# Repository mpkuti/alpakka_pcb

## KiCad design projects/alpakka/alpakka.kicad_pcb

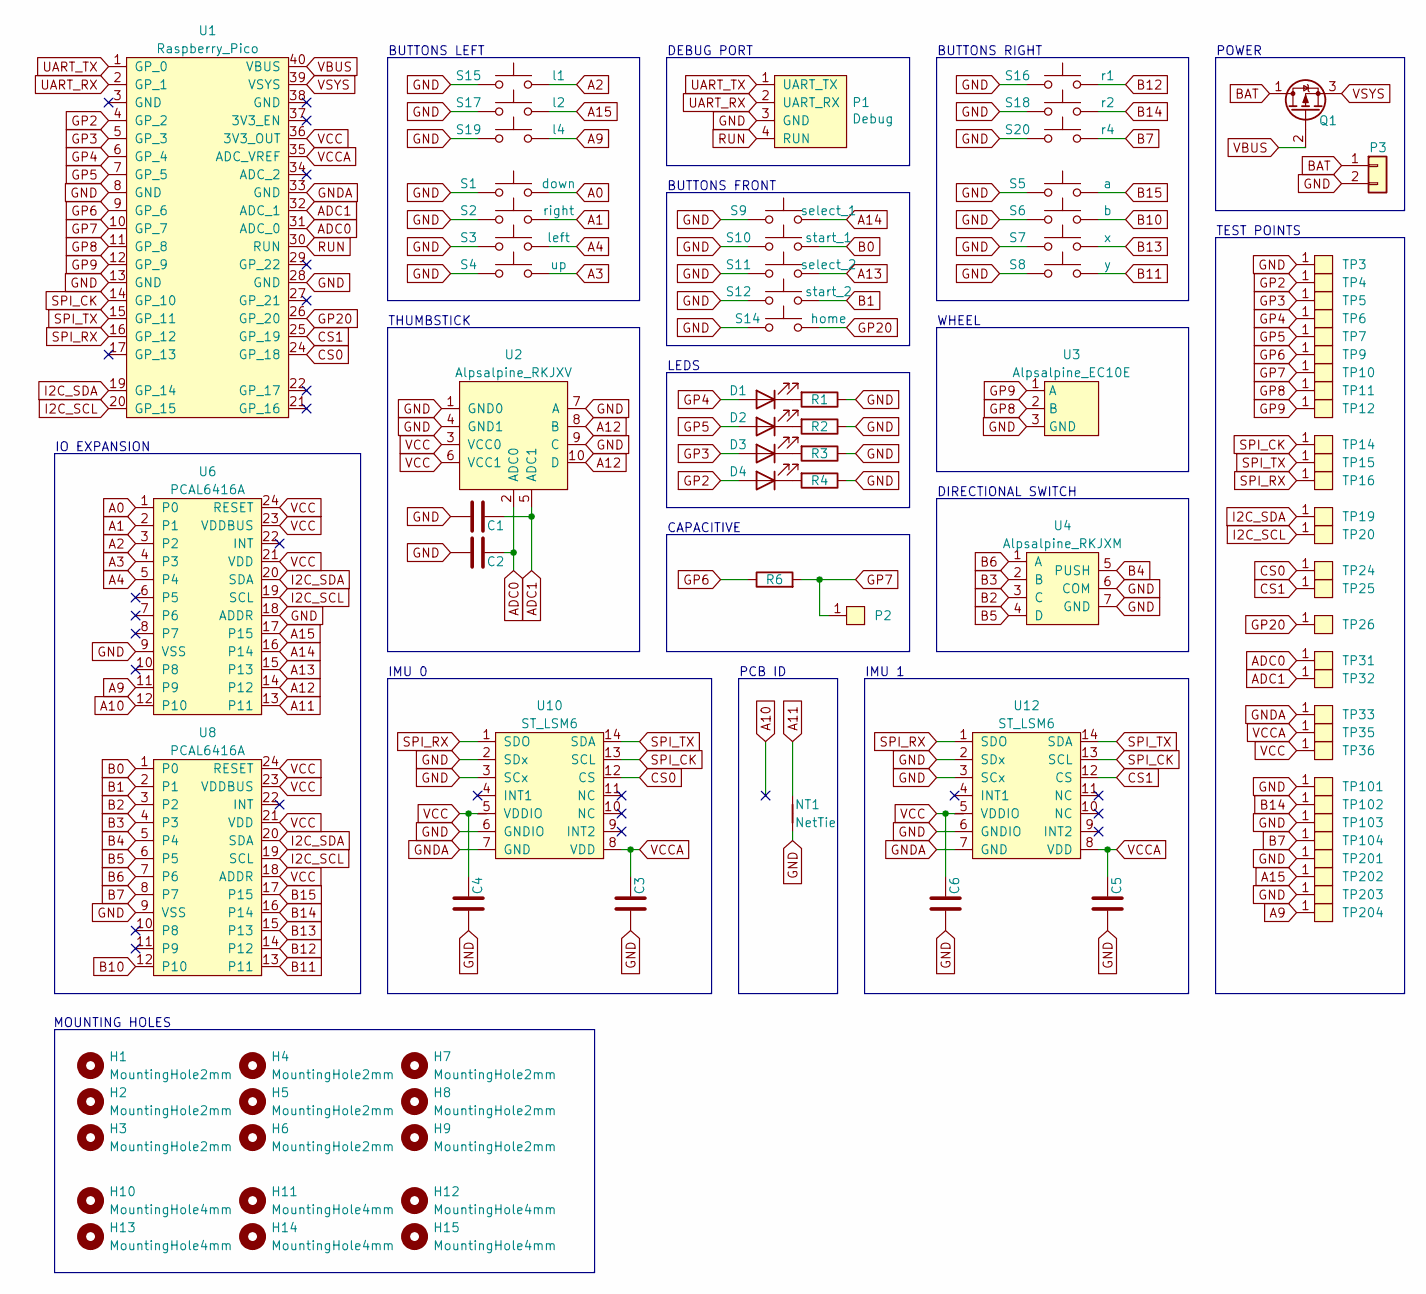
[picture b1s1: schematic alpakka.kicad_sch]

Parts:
C1, C2, C3, C4, C5, C6: 0.1µF; C_0402_1005Metric_Pad0.74x0.62mm_HandSolder; LCSC C1525
D1, D2, D3, D4: Diode; D_0603_1608Metric_Pad1.05x0.95mm_HandSolder; LCSC C2290
H1, H2, H3, H4, H5, H6, H7, H8, H9: MountingHole2mm; NPTH_2mm
H10, H11, H12, H13, H14, H15: MountingHole4mm; NPTH_4mm
NT1: NetTie; NetTie-2_SMD_Pad0.5mm
P1: Debug; JST_S4B-PH-SM4-K-TB; mouser# 306-S4BPHSM4KTBLFSN; LCSC C265332
P2: Endpoint; 304D-262503; LCSC C707322
P3: Conn_01x02; JST_PH_2_TH
Q1: Q_PMOS_DGS; SOT-23-DGS; digikey# DMG2305UX-7DICT-ND
R1, R2, R3, R4: 20Ω; R_0603_1608Metric_Pad0.98x0.95mm_HandSolder; LCSC C22950
R6: 510kΩ; R_0402_1005Metric_Pad0.72x0.64mm_HandSolder; LCSC C11616
S1: down; Alpsalpine_SKPM; LCSC C115348
S2: right; Alpsalpine_SKPM; LCSC C115348
S3: left; Alpsalpine_SKPM; LCSC C115348
S4: up; Alpsalpine_SKPM; LCSC C115348
S5: a; Alpsalpine_SKPM; LCSC C115348
S6: b; Alpsalpine_SKPM; LCSC C115348
S7: x; Alpsalpine_SKPM; LCSC C115348
S8: y; Alpsalpine_SKPM; LCSC C115348
S9: select_1; Alpsalpine_SKPM; LCSC C115348
S10: start_1; Alpsalpine_SKPM; LCSC C115348
S11: select_2; Alpsalpine_SKPM; LCSC C115348
S12: start_2; Alpsalpine_SKPM; LCSC C115348
S14: home; Alpsalpine_SKPM; LCSC C115348
S15: l1; Alpsalpine_SKHHL; LCSC C125031
S16: r1; Alpsalpine_SKHHL; LCSC C125031
S17: l2; Alpsalpine_SKQG; LCSC C202424
S18: r2; Alpsalpine_SKQG; LCSC C202424
S19: l4; Alpsalpine_SKQG; LCSC C202424
S20: r4; Alpsalpine_SKQG; LCSC C202424
TP3, TP4, TP5, TP6, TP7, TP9, TP10, TP11, TP12, TP14, TP15, TP16, TP19, TP20, TP24, TP25, TP26, TP31, TP32, TP33, TP35, TP36, TP101, TP102, TP103, TP104, TP201, TP202, TP203, TP204: Endpoint; Pad_1mm
U1: Raspberry_Pico; LCSC C7203002
U2: Alpsalpine_RKJXV; Alpsalpine_RKJXV122400R; mouser# 688-RKJXV122400R; LCSC C918854
U3: Alpsalpine_EC10E; LCSC C110291
U4: Alpsalpine_RKJXM; Alpsalpine_RKJXM1015004; LCSC C97432
U6, U8: PCAL6416A; QFN24; LCSC C2652287
U10, U12: ST_LSM6; LGA14; LCSC C784817

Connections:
A0: S1.2, U6.1 (P0)
A1: S2.2, U6.2 (P1)
A2: S15.2, U6.3 (P2)
A3: S4.2, U6.4 (P3)
A4: S3.2, U6.5 (P4)
A9: S19.2, TP204.1, U6.11 (P9)
A10: U6.12 (P10)
A11: NT1.2, U6.13 (P11)
A12: U2.8 (B), U2.10 (D), U6.14 (P12)
A13: S11.2, U6.15 (P13)
A14: S9.2, U6.16 (P14)
A15: S17.2, TP202.1, U6.17 (P15)
ADC0: C2.2, TP31.1, U1.31 (ADC_0), U2.2 (ADC0)
ADC1: C1.2, TP32.1, U1.32 (ADC_1), U2.5 (ADC1)
B0: S10.2, U8.1 (P0)
B1: S12.2, U8.2 (P1)
B2: U4.3 (C), U8.3 (P2)
B3: U4.2 (B), U8.4 (P3)
B4: U4.5 (PUSH), U8.5 (P4)
B5: U4.4 (D), U8.6 (P5)
B6: U4.1 (A), U8.7 (P6)
B7: S20.2, TP104.1, U8.8 (P7)
B10: S6.2, U8.12 (P10)
B11: S8.2, U8.13 (P11)
B12: S16.2, U8.14 (P12)
B13: S7.2, U8.15 (P13)
B14: S18.2, TP102.1, U8.16 (P14)
B15: S5.2, U8.17 (P15)
BAT: P3.1, Q1.1 (D)
CS0: TP24.1, U1.24 (GP_18), U10.12 (CS)
CS1: TP25.1, U1.25 (GP_19), U12.12 (CS)
GND: C1.1, C2.1, C3.1, C4.1, C5.1, C6.1, NT1.1, P1.3 (GND), P3.2, R1.1, R2.1, R3.1, R4.1, S1.1, S2.1, S3.1, S4.1, S5.1, S6.1, S7.1, S8.1, S9.1, S10.1, S11.1, S12.1, S14.1, S15.1, S16.1, S17.1, S18.1, S19.1, S20.1, TP3.1, TP101.1, TP103.1, TP201.1, TP203.1, U1.8 (GND), U1.13 (GND), U1.28 (GND), U2.1 (GND0), U2.4 (GND1), U2.7 (A), U2.9 (C), U3.3 (GND), U4.6 (COM), U4.7 (GND), U6.9 (VSS), U6.18 (ADDR), U8.9 (VSS), U10.2 (SDx), U10.3 (SCx), U10.6 (GNDIO), U12.2 (SDx), U12.3 (SCx), U12.6 (GNDIO)
GNDA: TP33.1, U1.33 (GND), U10.7 (GND), U12.7 (GND)
GP2: D4.2 (A), TP4.1, U1.4 (GP_2)
GP3: D3.2 (A), TP5.1, U1.5 (GP_3)
GP4: D1.2 (A), TP6.1, U1.6 (GP_4)
GP5: D2.2 (A), TP7.1, U1.7 (GP_5)
GP6: R6.1, TP9.1, U1.9 (GP_6)
GP7: P2.1, R6.2, TP10.1, U1.10 (GP_7)
GP8: TP11.1, U1.11 (GP_8), U3.2 (B)
GP9: TP12.1, U1.12 (GP_9), U3.1 (A)
GP20: S14.2, TP26.1, U1.26 (GP_20)
I2C_SCL: TP20.1, U1.20 (GP_15), U6.19 (SCL), U8.19 (SCL)
I2C_SDA: TP19.1, U1.19 (GP_14), U6.20 (SDA), U8.20 (SDA)
unnamed: D1.1 (K), R1.2
unnamed: D2.1 (K), R2.2
unnamed: D3.1 (K), R3.2
unnamed: D4.1 (K), R4.2
RUN: P1.4 (RUN), U1.30 (RUN)
SPI_CK: TP14.1, U1.14 (GP_10), U10.13 (SCL), U12.13 (SCL)
SPI_RX: TP16.1, U1.16 (GP_12), U10.1 (SDO), U12.1 (SDO)
SPI_TX: TP15.1, U1.15 (GP_11), U10.14 (SDA), U12.14 (SDA)
UART_RX: P1.2 (UART_RX), U1.2 (GP_1)
UART_TX: P1.1 (UART_TX), U1.1 (GP_0)
VBUS: Q1.2 (G), U1.40 (VBUS)
VCC: C4.2, C6.2, TP36.1, U1.36 (3V3_OUT), U2.3 (VCC0), U2.6 (VCC1), U6.21 (VDD), U6.23 (VDDBUS), U6.24 (RESET), U8.18 (ADDR), U8.21 (VDD), U8.23 (VDDBUS), U8.24 (RESET), U10.5 (VDDIO), U12.5 (VDDIO)
VCCA: C3.2, C5.2, TP35.1, U1.35 (ADC_VREF), U10.8 (VDD), U12.8 (VDD)
VSYS: Q1.3 (S), U1.39 (VSYS)

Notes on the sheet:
WHEEL
DEBUG PORT
THUMBSTICK
IMU 0
PCB ID
IMU 1
BUTTONS FRONT
TEST POINTS
MOUNTING HOLES
DIRECTIONAL SWITCH
CAPACITIVE
IO EXPANSION
LEDS
BUTTONS LEFT
BUTTONS RIGHT
POWER

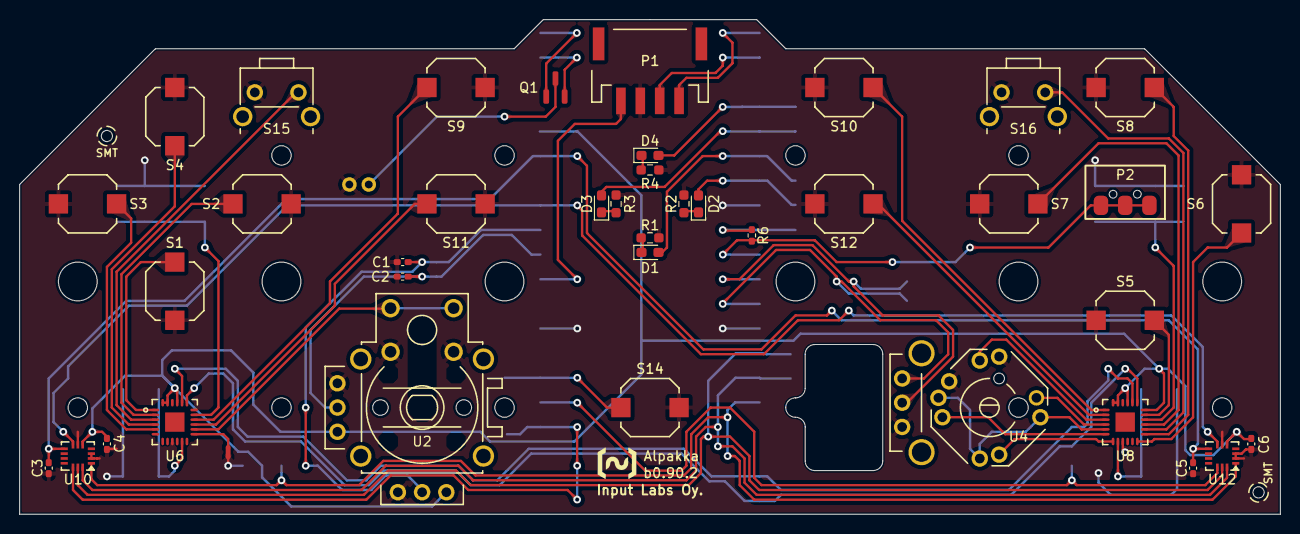
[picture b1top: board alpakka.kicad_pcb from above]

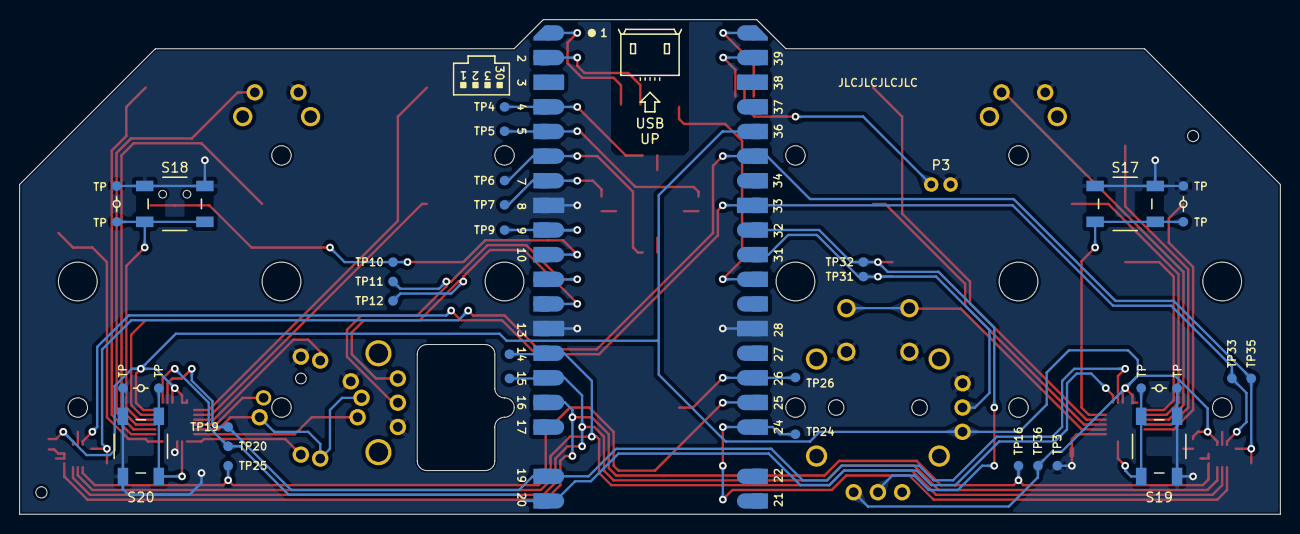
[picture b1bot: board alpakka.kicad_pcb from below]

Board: 2 copper layers, 130.0 x 51.0 mm, 92 parts (36 on the bottom side), 57 nets.

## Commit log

2024-04-15 Project updated to kicad 8.0, Moved project into projects folder
2024-12-04 fill some order info to BOM, also add 3d models of some parts
2024-12-05 add joystick 3d model and order info
2024-12-05 add info + 3d model for the right joystick
2024-12-05 replace capacitive contact part with one with 3d model
2024-12-05 ignore lock files
2024-12-05 add resistor order info
2024-12-05 mod button keepout zone
2024-12-05 add 3d model of the debug connector
2024-12-09 add Rpi Pico 3d model, also other mods
